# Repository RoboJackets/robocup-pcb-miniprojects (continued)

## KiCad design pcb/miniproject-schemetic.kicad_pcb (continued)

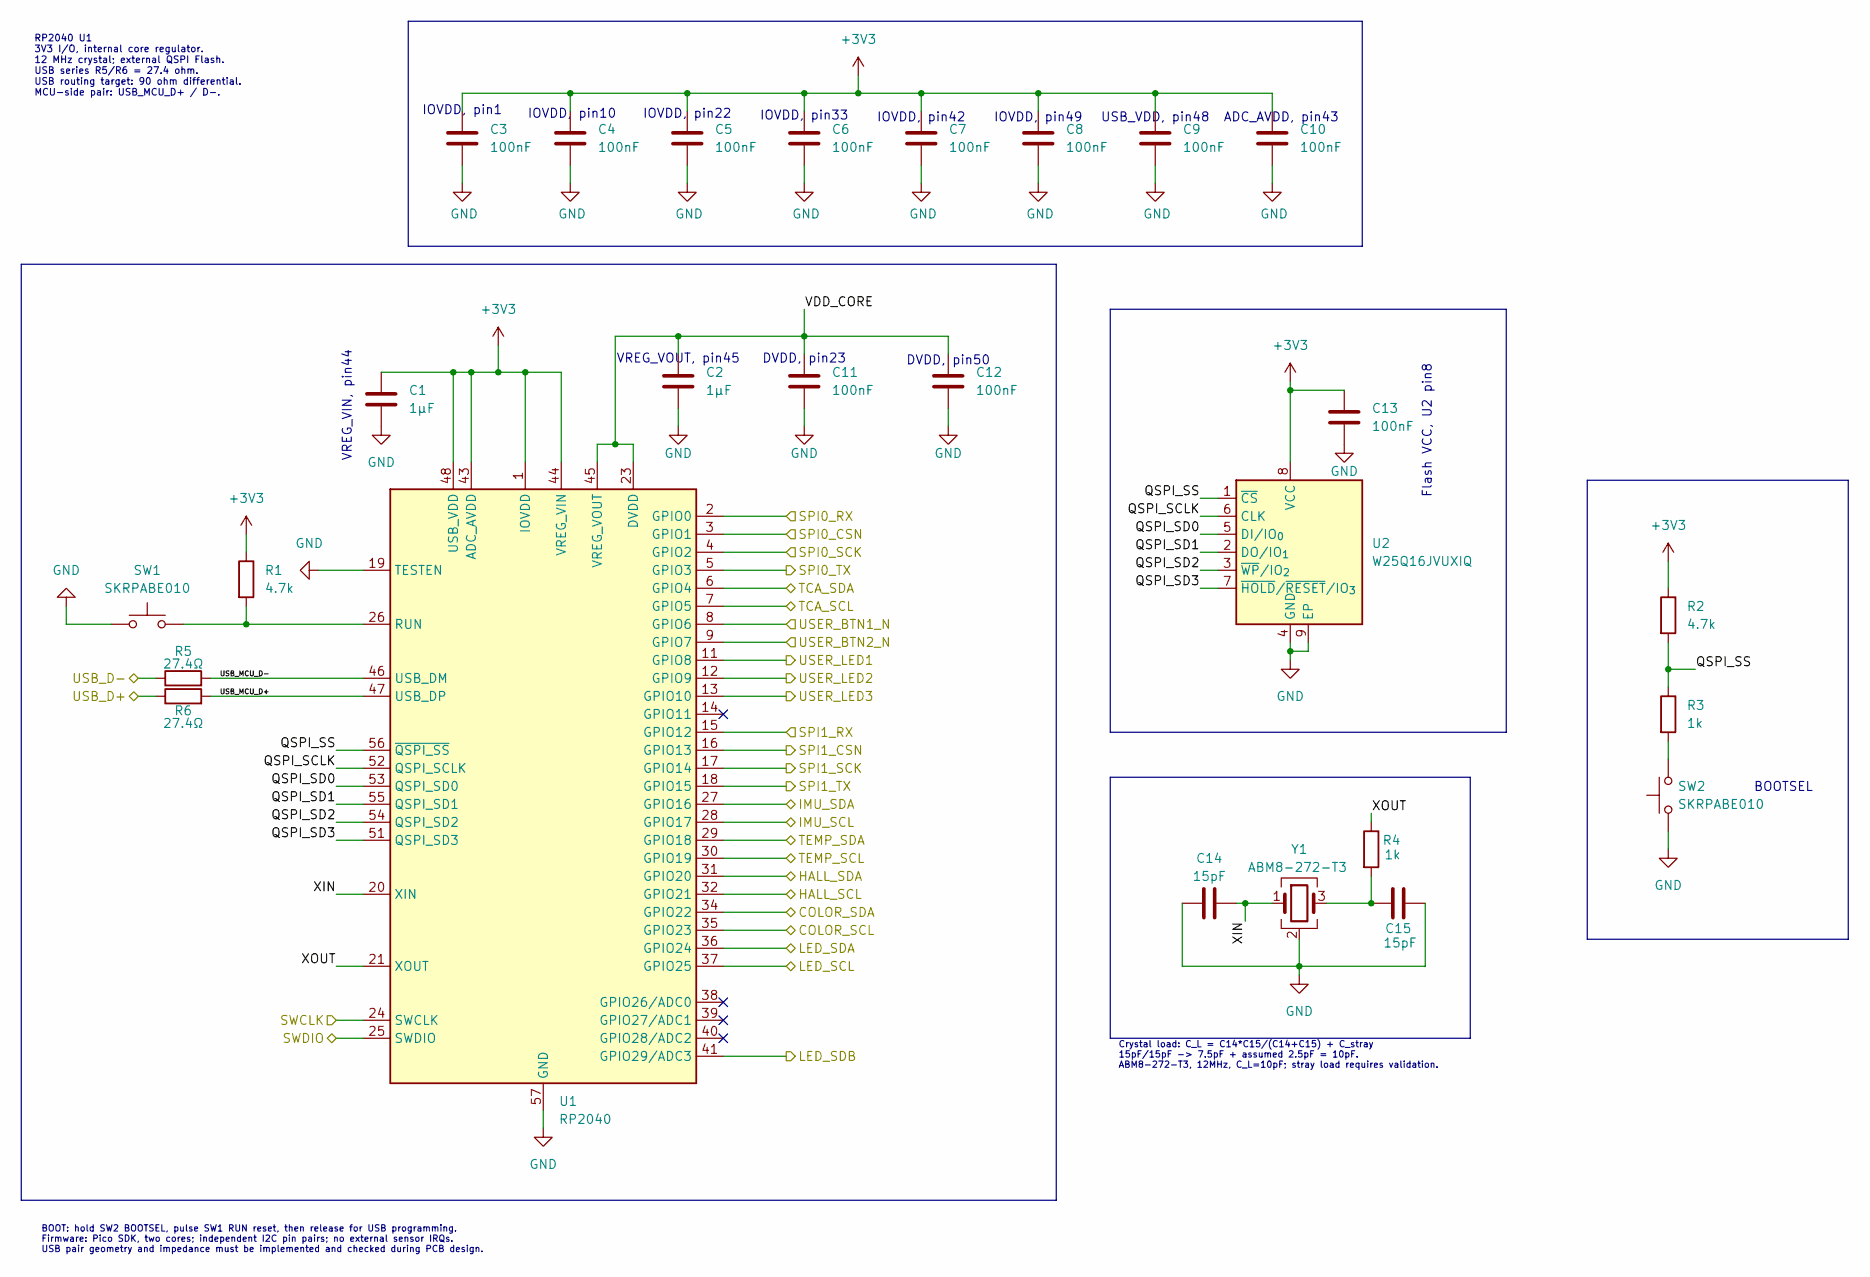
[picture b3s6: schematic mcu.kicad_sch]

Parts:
C1, C2: 1µF; C_0603_1608Metric; Tolerance 10%; Voltage 6.3V minimum
C3, C4, C5, C6, C7, C8, C9, C10, C11, C12, C13: 100nF; C_0603_1608Metric; Tolerance 10%; Voltage 6.3V minimum
C14, C15: 15pF; C_0603_1608Metric; Tolerance 5%; Voltage 6.3V minimum
R1, R2: 4.7k; R_0603_1608Metric; Tolerance 1%
R3, R4: 1k; R_0603_1608Metric; Tolerance 1%
R5, R6: 27.4Ω; R_0603_1608Metric; Tolerance 1%
SW1, SW2: SKRPABE010; SW_SPST_ALPS_SKRPABE010_4.2x3.2mm
U1: RP2040; QFN-56-1EP_7x7mm_P0.4mm_EP3.2x3.2mm
U2: W25Q16JVUXIQ; Winbond_USON-8-1EP_3x2mm_P0.5mm_EP0.2x1.6mm
Y1: ABM8-272-T3; Crystal_SMD_3225-4Pin_3.2x2.5mm

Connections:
+3V3: C1.1, C3.1, C4.1, C5.1, C6.1, C7.1, C8.1, C9.1, C10.1, C13.1, R1.1, R2.1, U1.1 (IOVDD), U1.10 (IOVDD), U1.22 (IOVDD), U1.33 (IOVDD), U1.42 (IOVDD), U1.43 (ADC_AVDD), U1.44 (VREG_VIN), U1.48 (USB_VDD), U1.49 (IOVDD), U2.8 (VCC); also elsewhere on the board
/COLOR_SCL: U1.35 (GPIO23); also elsewhere on the board
/COLOR_SDA: U1.34 (GPIO22); also elsewhere on the board
/HALL_SCL: U1.32 (GPIO21); also elsewhere on the board
/HALL_SDA: U1.31 (GPIO20); also elsewhere on the board
/IMU_SCL: U1.28 (GPIO17); also elsewhere on the board
/IMU_SDA: U1.27 (GPIO16); also elsewhere on the board
/Interfaces/USB_D+: R6.1; also elsewhere on the board
/Interfaces/USB_D-: R5.1; also elsewhere on the board
/LED_SCL: U1.37 (GPIO25); also elsewhere on the board
/LED_SDA: U1.36 (GPIO24); also elsewhere on the board
/LED_SDB: U1.41 (GPIO29/ADC3); also elsewhere on the board
/MCU/QSPI_SCLK: U1.52 (QSPI_SCLK), U2.6 (CLK)
/MCU/QSPI_SD0: U1.53 (QSPI_SD0), U2.5 (DI/IO_{0})
/MCU/QSPI_SD1: U1.55 (QSPI_SD1), U2.2 (DO/IO_{1})
/MCU/QSPI_SD2: U1.54 (QSPI_SD2), U2.3 (~WP/IO_{2})
/MCU/QSPI_SD3: U1.51 (QSPI_SD3), U2.7 (~HOLD/~RESET/IO_{3})
/MCU/QSPI_SS: R2.2, R3.1, U1.56 (~QSPI_SS), U2.1 (~CS)
/MCU/USB_MCU_D+: R6.2, U1.47 (USB_DP)
/MCU/USB_MCU_D-: R5.2, U1.46 (USB_DM)
/MCU/VDD_CORE: C2.1, C11.1, C12.1, U1.23 (DVDD), U1.45 (VREG_VOUT), U1.50 (DVDD)
/MCU/XIN: C14.2, U1.20 (XIN), Y1.1
/MCU/XOUT: R4.1, U1.21 (XOUT)
/SPI0_CSN: U1.3 (GPIO1); also elsewhere on the board
/SPI0_RX: U1.2 (GPIO0); also elsewhere on the board
/SPI0_SCK: U1.4 (GPIO2); also elsewhere on the board
/SPI0_TX: U1.5 (GPIO3); also elsewhere on the board
/SPI1_CSN: U1.16 (GPIO13); also elsewhere on the board
/SPI1_RX: U1.15 (GPIO12); also elsewhere on the board
/SPI1_SCK: U1.17 (GPIO14); also elsewhere on the board
/SPI1_TX: U1.18 (GPIO15); also elsewhere on the board
/SWCLK: U1.24 (SWCLK); also elsewhere on the board
/SWDIO: U1.25 (SWDIO); also elsewhere on the board
/TCA_SCL: U1.7 (GPIO5); also elsewhere on the board
/TCA_SDA: U1.6 (GPIO4); also elsewhere on the board
/TEMP_SCL: U1.30 (GPIO19); also elsewhere on the board
/TEMP_SDA: U1.29 (GPIO18); also elsewhere on the board
/USER_BTN1_N: U1.8 (GPIO6); also elsewhere on the board
/USER_BTN2_N: U1.9 (GPIO7); also elsewhere on the board
/USER_LED1: U1.11 (GPIO8); also elsewhere on the board
/USER_LED2: U1.12 (GPIO9); also elsewhere on the board
/USER_LED3: U1.13 (GPIO10); also elsewhere on the board
GND: C1.2, C2.2, C3.2, C4.2, C5.2, C6.2, C7.2, C8.2, C9.2, C10.2, C11.2, C12.2, C13.2, C14.1, C15.2, SW1.1, SW2.1, U1.19 (TESTEN), U1.57 (GND), U2.4 (GND), U2.9 (EP), Y1.2 (G), Y1.4 (G); also elsewhere on the board
unnamed: C15.1, R4.2, Y1.3
unnamed: R3.2, SW2.2
unnamed: R1.2, SW1.2, U1.26 (RUN)

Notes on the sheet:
DVDD, pin23
VREG_VIN, pin44
IOVDD, pin49
IOVDD, pin42
Flash VCC, U2 pin8
ADC_AVDD, pin43
DVDD, pin50
IOVDD, pin10
USB_VDD, pin48
IOVDD, pin33
IOVDD, pin22
BOOTSEL
IOVDD, pin1
VREG_VOUT, pin45
RP2040 U1 3V3 I/O, internal core regulator. 12 MHz crystal; external QSPI Flash. USB series R5/R6 = 27.4 ohm. USB routing target: 90 ohm differential. MCU-side pair: USB_MCU_D+ / D-.
Crystal load: C_L = C14*C15/(C14+C15) + C_stray 15pF/15pF -> 7.5pF + assumed 2.5pF = 10pF. ABM8-272-T3, 12MHz, C_L=10pF; stray load requires validation.
BOOT: hold SW2 BOOTSEL, pulse SW1 RUN reset, then release for USB programming. Firmware: Pico SDK, two cores; independent I2C pin pairs; no external sensor IRQs. USB pair geometry and impedance must be implemented and checked during PCB design.

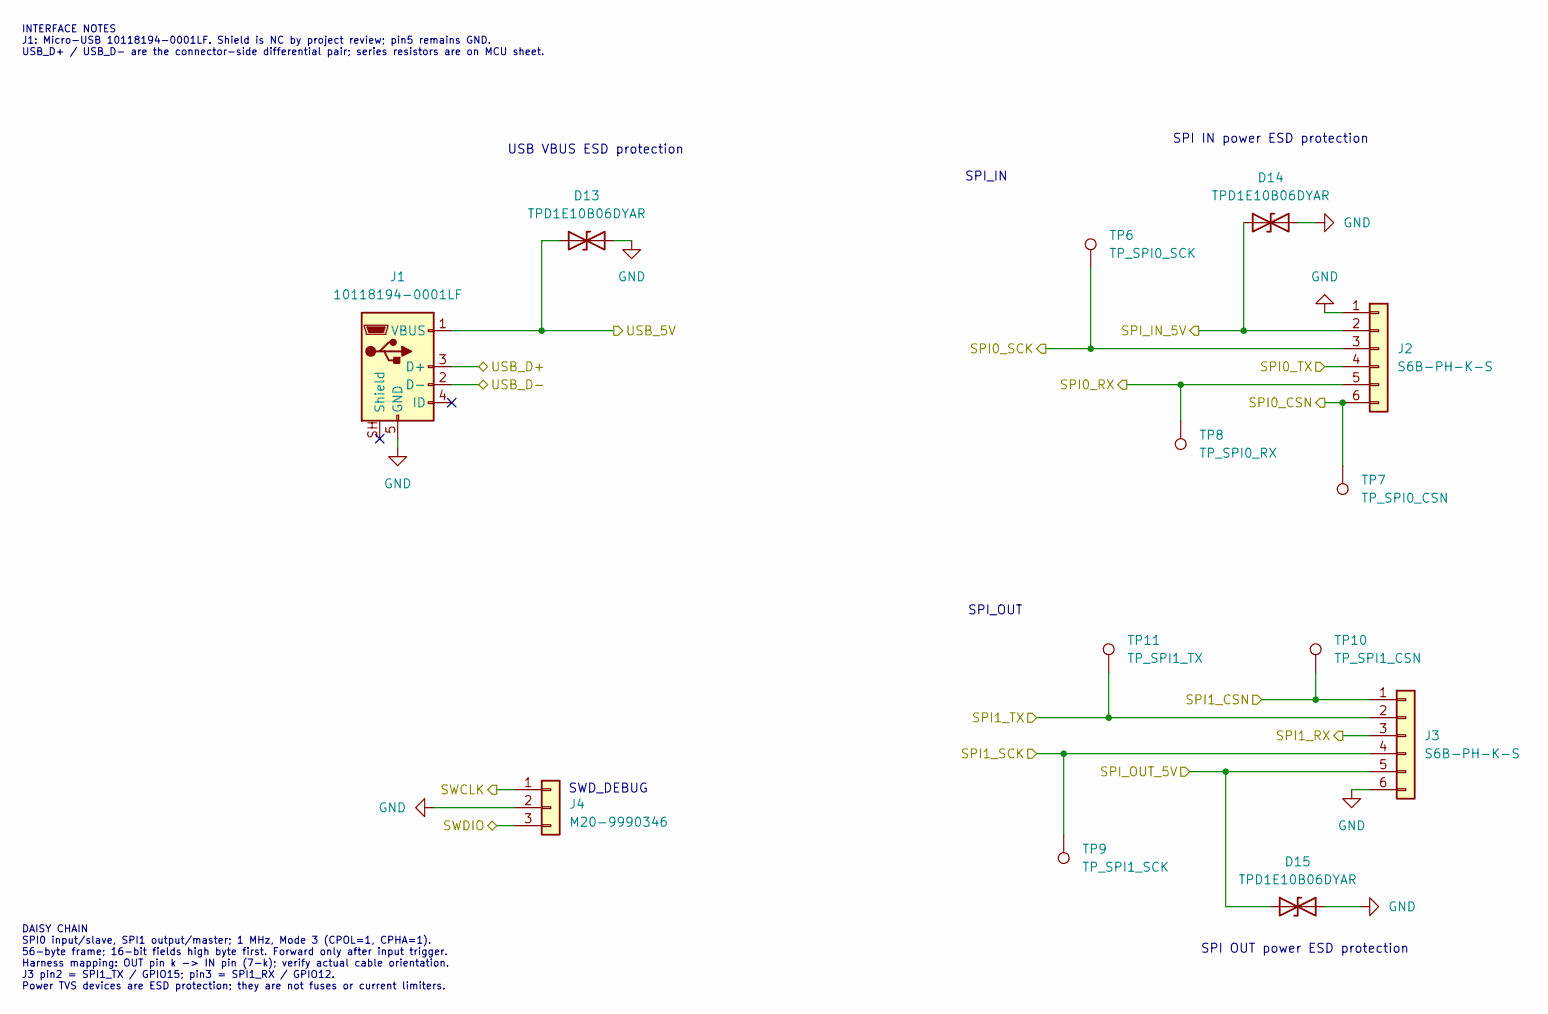
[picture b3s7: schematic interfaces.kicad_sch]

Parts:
D13, D14, D15: TPD1E10B06DYAR; D_SOD-523
J1: 10118194-0001LF; USB_Micro-B_Amphenol_10118194-0001LF_Horizontal
J2, J3: S6B-PH-K-S; JST_PH_S6B-PH-K_1x06_P2.00mm_Horizontal
J4: M20-9990346; PinHeader_1x03_P2.54mm_Vertical
TP6: TP_SPI0_SCK; TestPoint_Pad_D1.0mm
TP7: TP_SPI0_CSN; TestPoint_Pad_D1.0mm
TP8: TP_SPI0_RX; TestPoint_Pad_D1.0mm
TP9: TP_SPI1_SCK; TestPoint_Pad_D1.0mm
TP10: TP_SPI1_CSN; TestPoint_Pad_D1.0mm
TP11: TP_SPI1_TX; TestPoint_Pad_D1.0mm

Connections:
+5V: D15.1 (A1), J3.5; also elsewhere on the board
/Interfaces/USB_D+: J1.3 (D+); also elsewhere on the board
/Interfaces/USB_D-: J1.2 (D-); also elsewhere on the board
/SPI0_CSN: J2.6, TP7.1 (1_1); also elsewhere on the board
/SPI0_RX: J2.5, TP8.1 (1_1); also elsewhere on the board
/SPI0_SCK: J2.3, TP6.1 (1_1); also elsewhere on the board
/SPI0_TX: J2.4; also elsewhere on the board
/SPI1_CSN: J3.1, TP10.1 (1_1); also elsewhere on the board
/SPI1_RX: J3.3; also elsewhere on the board
/SPI1_SCK: J3.4, TP9.1 (1_1); also elsewhere on the board
/SPI1_TX: J3.2, TP11.1 (1_1); also elsewhere on the board
/SPI_IN_5V: D14.1 (A1), J2.2; also elsewhere on the board
/SWCLK: J4.1; also elsewhere on the board
/SWDIO: J4.3; also elsewhere on the board
/USB_5V: D13.1 (A1), J1.1 (VBUS); also elsewhere on the board
GND: D13.2 (A2), D14.2 (A2), D15.2 (A2), J1.5 (GND), J2.1, J3.6, J4.2; also elsewhere on the board

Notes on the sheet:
USB VBUS ESD protection
SPI_IN
SPI OUT power ESD protection
SPI IN power ESD protection
SPI_OUT
SWD_DEBUG
INTERFACE NOTES J1: Micro-USB 10118194-0001LF. Shield is NC by project review; pin5 remains GND. USB_D+ / USB_D- are the connector-side differential pair; series resistors are on MCU sheet.
DAISY CHAIN SPI0 input/slave, SPI1 output/master; 1 MHz, Mode 3 (CPOL=1, CPHA=1). 56-byte frame; 16-bit fields high byte first. Forward only after input trigger. Harness mapping: OUT pin k -> IN pin (7-k); verify actual cable orientation. J3 pin2 = SPI1_TX / GPIO15; pin3 = SPI1_RX / GPIO12. Power T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

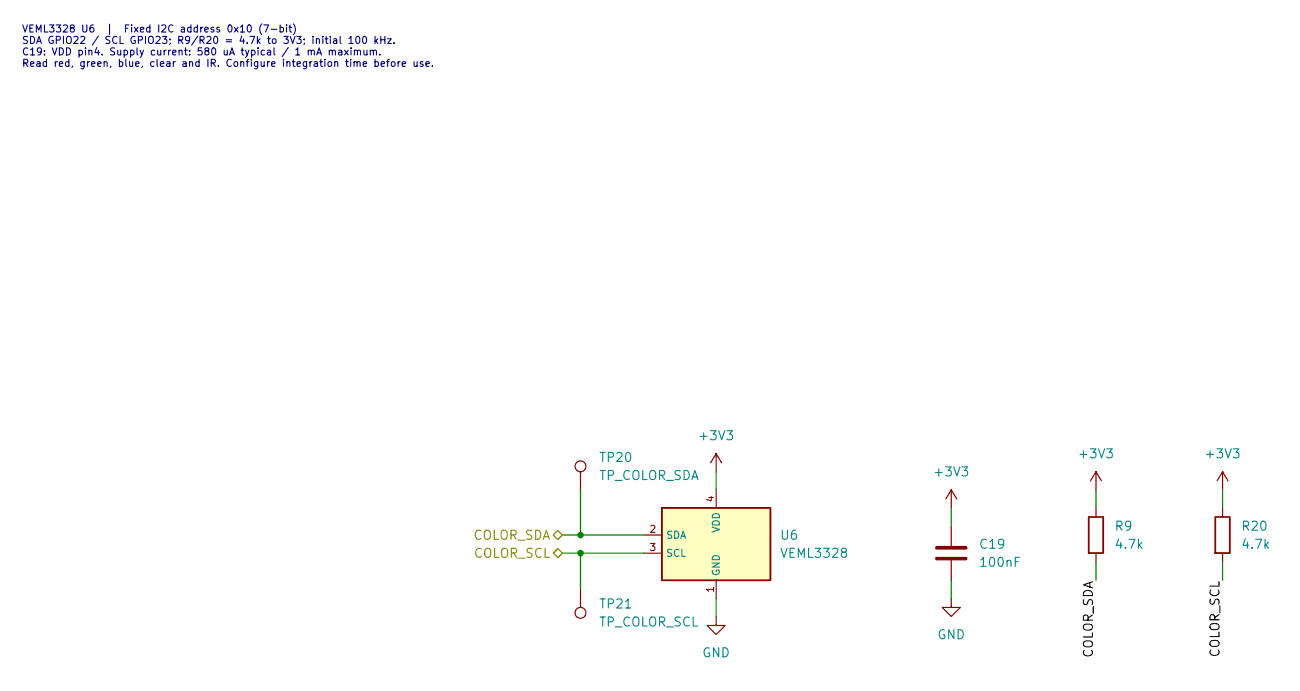
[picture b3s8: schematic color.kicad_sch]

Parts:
C19: 100nF; C_0603_1608Metric; Tolerance 10%; Voltage 6.3V minimum
R9, R20: 4.7k; R_0603_1608Metric; Tolerance 1%
TP20: TP_COLOR_SDA; TestPoint_Pad_D1.0mm
TP21: TP_COLOR_SCL; TestPoint_Pad_D1.0mm
U6: VEML3328; Vishay_VEML3328_2x1.25mm

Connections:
+3V3: C19.1, R9.1, R20.1, U6.4 (VDD); also elsewhere on the board
/COLOR_SCL: R20.2, TP21.1 (1_1), U6.3 (SCL); also elsewhere on the board
/COLOR_SDA: R9.2, TP20.1 (1_1), U6.2 (SDA); also elsewhere on the board
GND: C19.2, U6.1 (GND); also elsewhere on the board

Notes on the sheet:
VEML3328 U6 | Fixed I2C address 0x10 (7-bit) SDA GPIO22 / SCL GPIO23; R9/R20 = 4.7k to 3V3; initial 100 kHz. C19: VDD pin4. Supply current: 580 uA typical / 1 mA maximum. Read red, green, blue, clear and IR. Configure integration time before use.

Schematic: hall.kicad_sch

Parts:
C17: 100nF; C_0603_1608Metric; Tolerance 10%; Voltage 6.3V minimum
R15, R16, R17: 4.7k; R_0603_1608Metric; Tolerance 1%
TP18: TP_HALL_SCL; TestPoint_Pad_D1.0mm
TP19: TP_HALL_SDA; TestPoint_Pad_D1.0mm
U4: TMAG5273A2QDBVR; SOT-23-6

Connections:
+3V3: C17.1, R15.2, R16.1, R17.1, U4.4 (VCC); also elsewhere on the board
/HALL_SCL: R15.1, TP18.1 (1_1), U4.1 (SCL); also elsewhere on the board
/HALL_SDA: R16.2, TP19.1 (1_1), U4.6 (SDA); also elsewhere on the board
GND: C17.2, U4.2 (GND), U4.3 (TEST); also elsewhere on the board
unnamed: R17.2, U4.5 (~INT)

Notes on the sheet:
TMAG5273A2 U4 | Factory I2C address 0x35 (7-bit) SDA GPIO20 / SCL GPIO21; R15/R16 = 4.7k to 3V3; initial 100 kHz. A2 range option: +/-133 mT or +/-266 mT. Active current: 2.3 mA typical. C17: VCC pin4; TEST pin3 is GND. INT pin5 has R17 pullup only, no MCU IRQ. Firmware: INT_MODE = 0; use I2C trigg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

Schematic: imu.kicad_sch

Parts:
C20: 10nF; C_0603_1608Metric; Tolerance 10%; Voltage 6.3V minimum
C21: 100nF; C_0603_1608Metric; Tolerance 10%; Voltage 6.3V minimum
C22: 2.2µF; C_0603_1608Metric; Tolerance 10%; Voltage 6.3V minimum
R21, R22: 4.7k; R_0603_1608Metric; Tolerance 1%
TP14: TP_IMU_SDA; TestPoint_Pad_D1.0mm
TP15: TP_IMU_SCL; TestPoint_Pad_D1.0mm
U7: ICM-42605; LGA-14_3x2.5mm_P0.5mm_LayoutBorder3x4y

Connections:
+3V3: C20.1, C21.1, C22.1, R21.1, R22.1, U7.5 (VDDIO), U7.8 (VDD), U7.12 (~AP_CS); also elsewhere on the board
/IMU_SCL: R22.2, TP15.1 (1_1), U7.13 (AP_SCL); also elsewhere on the board
/IMU_SDA: R21.2, TP14.1 (1_1), U7.14 (AP_SDA); also elsewhere on the board
GND: C20.2, C21.2, C22.2, U7.1 (AP_AD0/SDO), U7.6 (GND), U7.7 (RESV), U7.9 (INT2/FSYNC); also elsewhere on the board

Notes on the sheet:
VDDIO, pin5
VDD, pin8
ICM-42605 U7 | I2C address 0x68 (7-bit), AP_AD0 pin1 = GND AP_CS pin12 = 3V3 for I2C. SDA GPIO16 / SCL GPIO17; R21/R22 = 4.7k. Initial bus speed 100 kHz. AP_AD0 is an input in this configuration. INT1 pin4 is NC. Pin9 is unused FSYNC: GND per TDK pin-function table. Firmware must keep pin9 as an in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

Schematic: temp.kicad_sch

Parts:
C18: 100nF; C_0603_1608Metric; Tolerance 10%; Voltage 6.3V minimum
R18, R19: 4.7k; R_0603_1608Metric; Tolerance 1%
TP16: TP_TEMP_SDA; TestPoint_Pad_D1.0mm
TP17: TP_TEMP_SCL; TestPoint_Pad_D1.0mm
U5: LM75ADP; TSSOP-8_3x3mm_P0.65mm

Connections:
+3V3: C18.1, R18.1, R19.1, U5.8 (VCC); also elsewhere on the board
/TEMP_SCL: R19.2, TP17.1 (1_1), U5.2 (SCL); also elsewhere on the board
/TEMP_SDA: R18.2, TP16.1 (1_1), U5.1 (SDA); also elsewhere on the board
GND: C18.2, U5.4 (GND), U5.5 (A2), U5.6 (A1), U5.7 (A0); also elsewhere on the board

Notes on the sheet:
LM75ADP U5 | I2C address 0x48 (7-bit), A2:A0 = 000 SDA GPIO18 / SCL GPIO19; R18/R19 = 4.7k to 3V3; initial 100 kHz. C18: VCC pin8. OS pin3 is NC; poll temperature over I2C. Supply current: 100 uA typical with inactive bus; 1 mA maximum with active bus. NXP LM75A register format: signed temperature;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

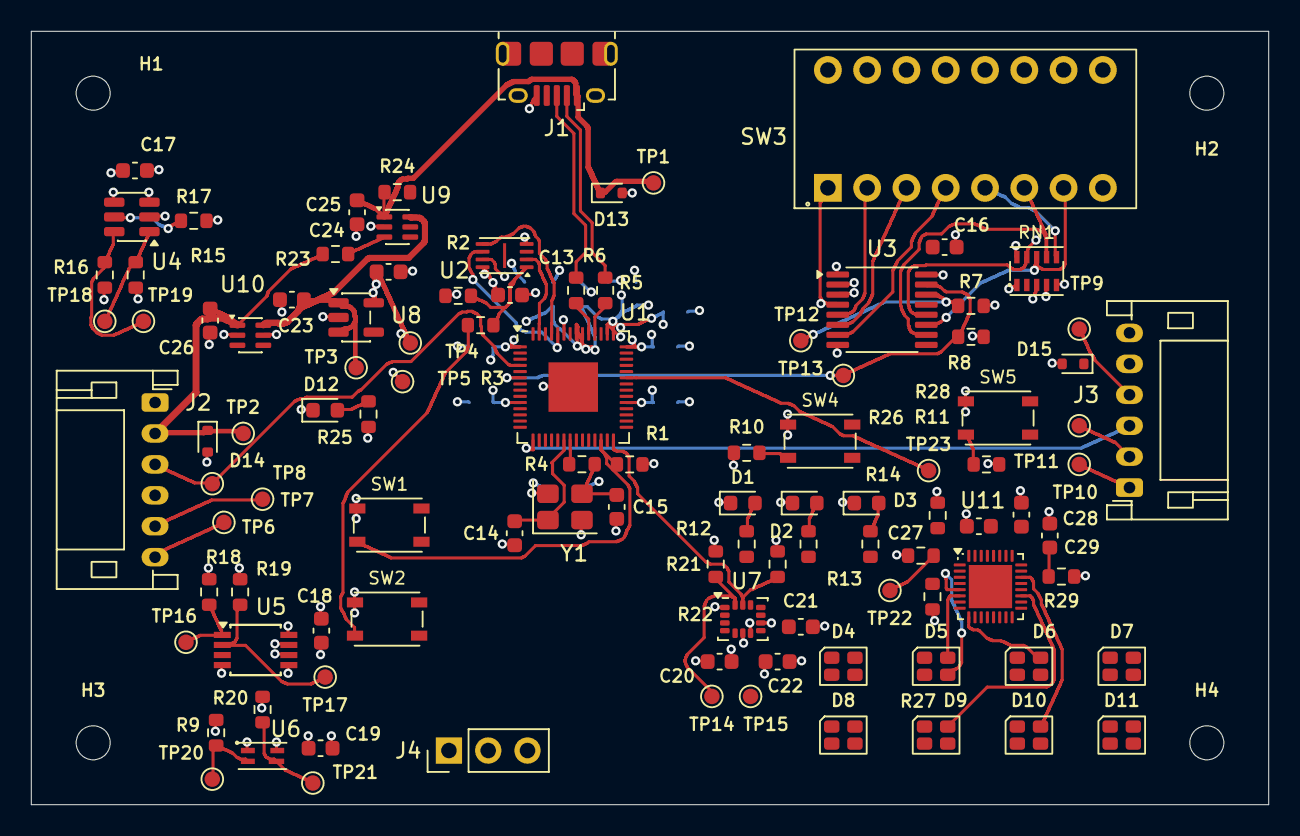
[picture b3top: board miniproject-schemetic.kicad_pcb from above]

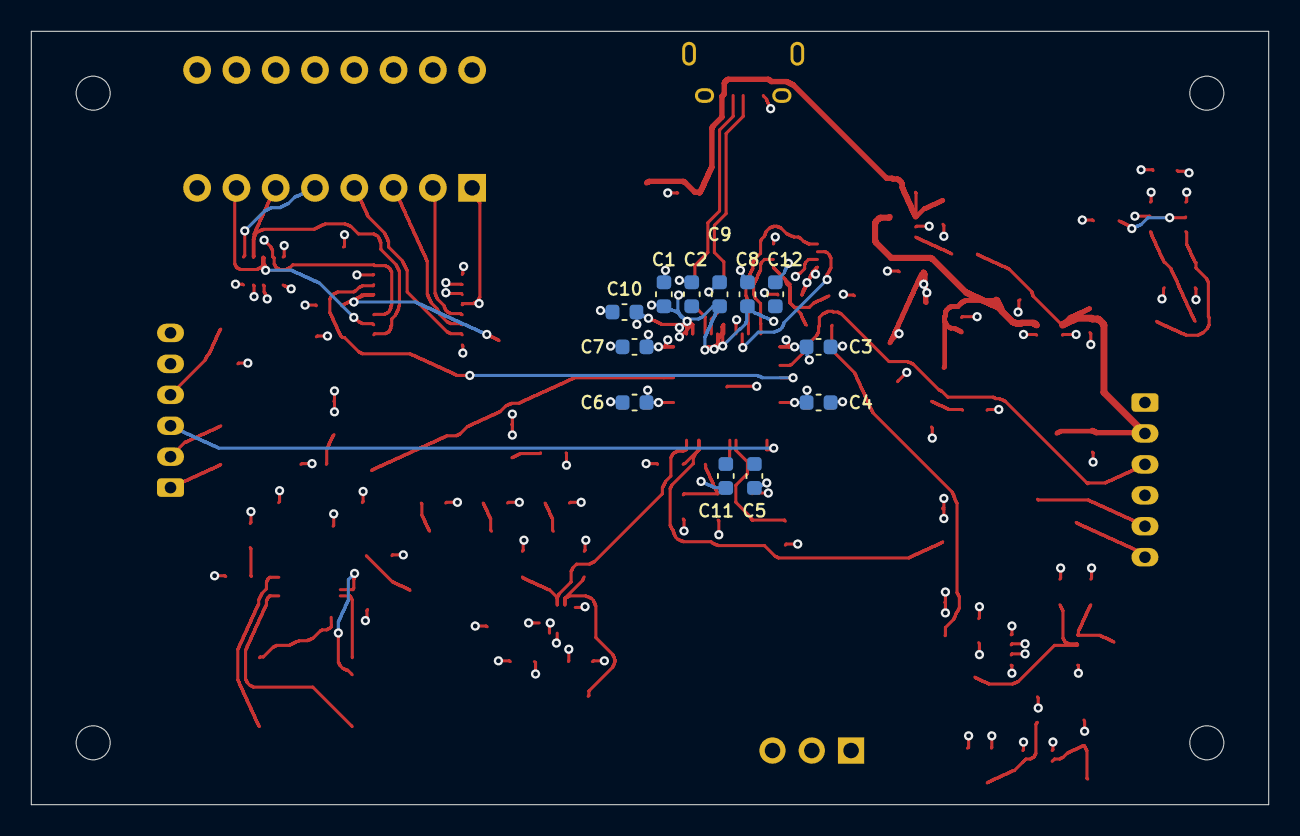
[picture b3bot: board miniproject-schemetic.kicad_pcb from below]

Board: 4 copper layers, 80.0 x 50.0 mm, 122 parts (12 on the bottom side), 89 nets.

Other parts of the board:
H1, H2, H3, H4: MountingHole_2.2mm_M2

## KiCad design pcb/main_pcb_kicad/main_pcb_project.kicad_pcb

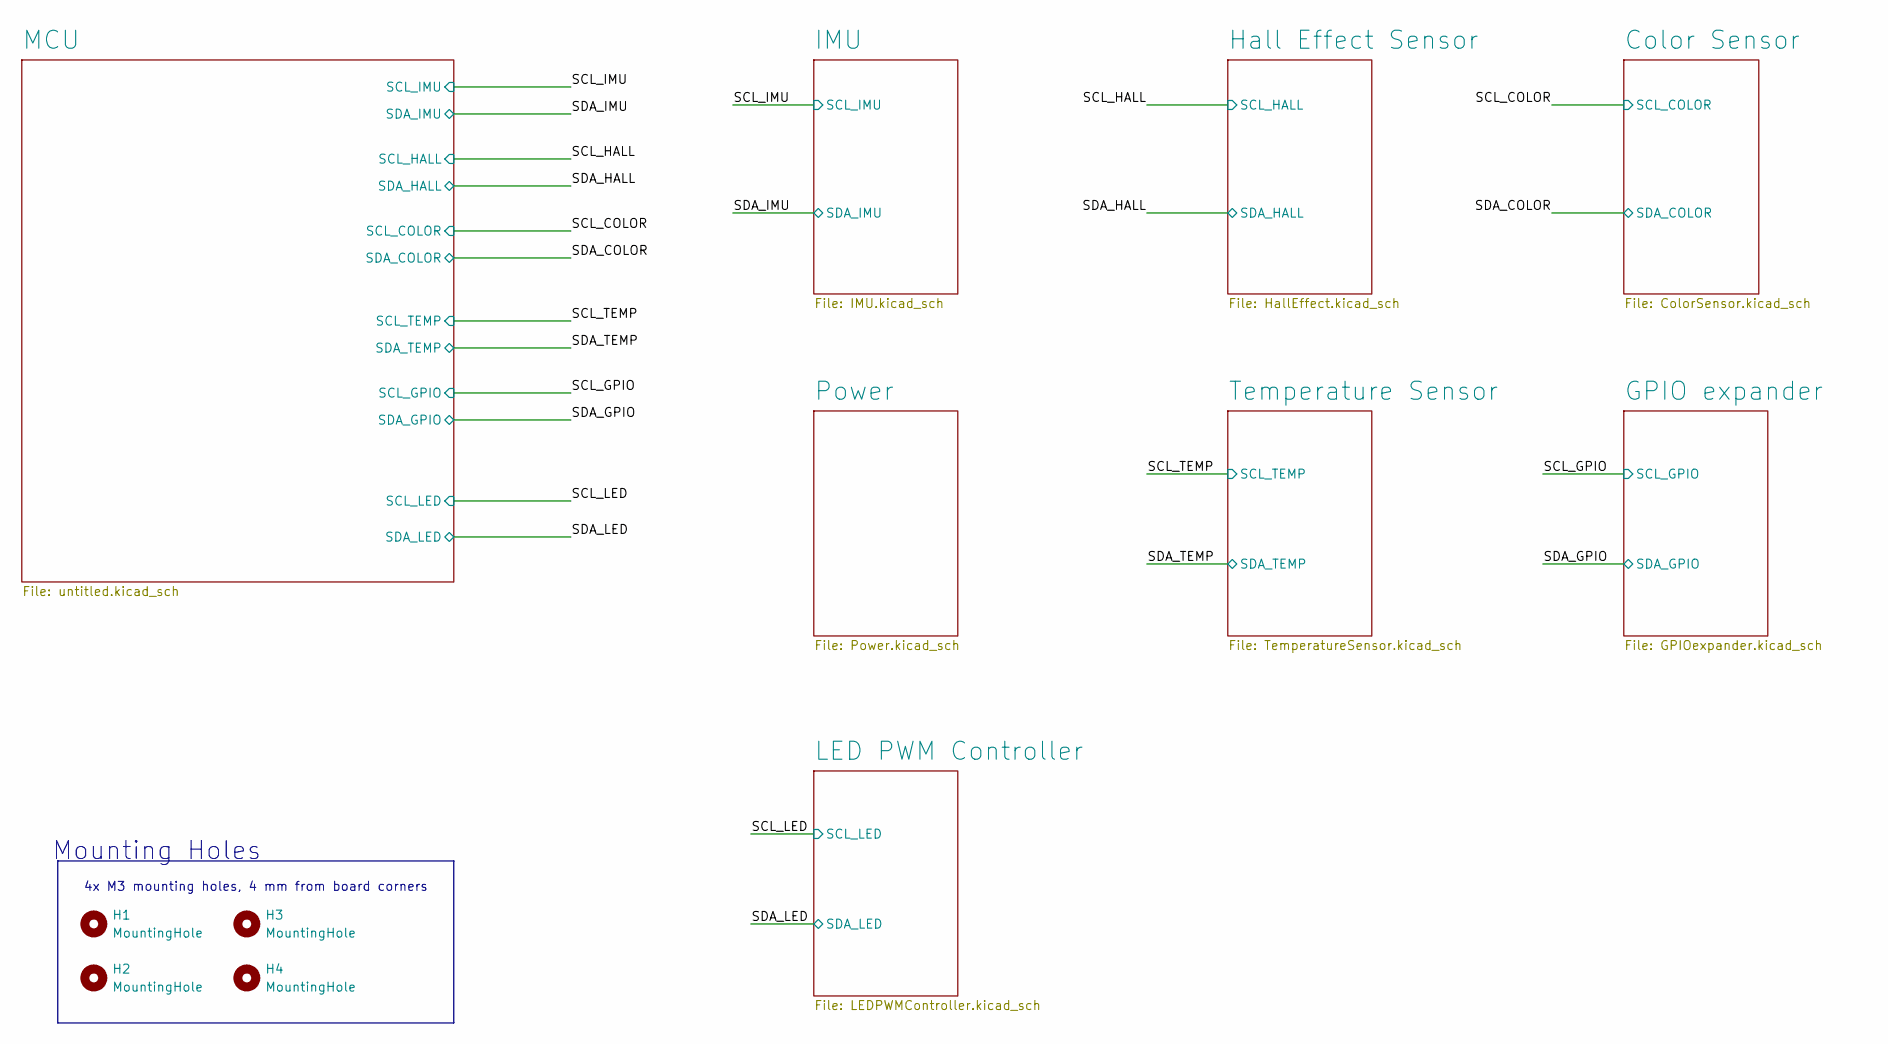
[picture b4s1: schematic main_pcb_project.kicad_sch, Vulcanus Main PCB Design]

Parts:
H1, H2, H3, H4: MountingHole; MountingHole_3.2mm_M3

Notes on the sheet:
Mounting Holes
4x M3 mounting holes, 4 mm from board corners

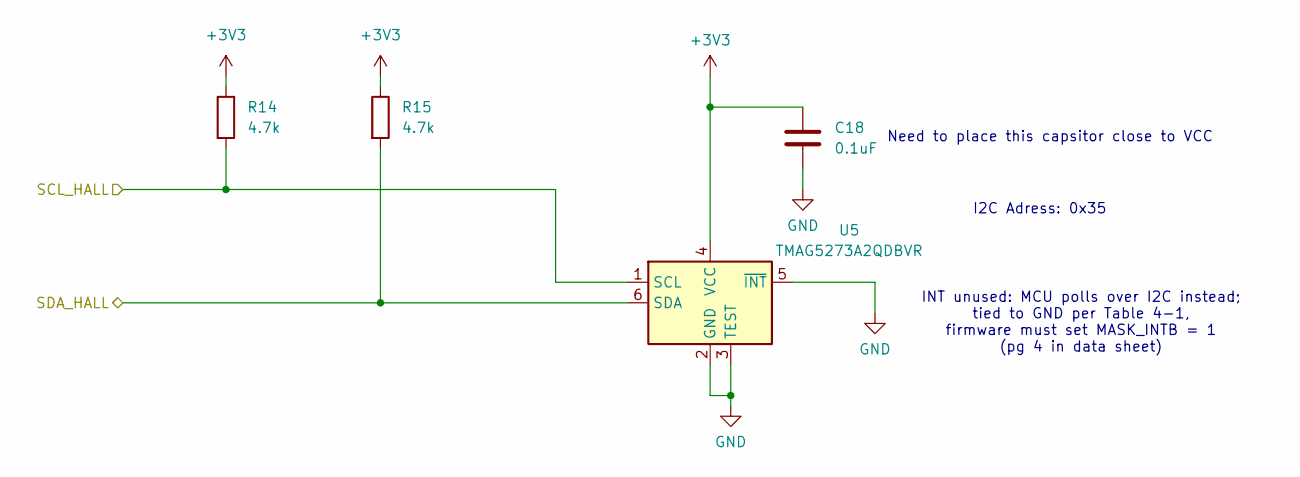
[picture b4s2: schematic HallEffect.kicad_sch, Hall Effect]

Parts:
C18: 0.1uF; C_0603_1608Metric; Manufacturer P/N CL10B104KB8NNNC
R14, R15: 4.7k; R_0402_1005Metric; Manufacturer P/N RC0402FR-074K7L
U5: TMAG5273A2QDBVR; SOT-23-6; Manufacturer P/N TMAG5273A2QDBVR

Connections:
+3V3: C18.1, R14.1, R15.1, U5.4 (VCC); also elsewhere on the board
/SCL_HALL: R14.2, U5.1 (SCL); also elsewhere on the board
/SDA_HALL: R15.2, U5.6 (SDA); also elsewhere on the board
GND: C18.2, U5.2 (GND), U5.3 (TEST), U5.5 (~INT); also elsewhere on the board

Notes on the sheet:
INT unused: MCU polls over I2C instead; tied to GND per Table 4-1, firmware must set MASK_INTB = 1 (pg 4 in data sheet)
Need to place this capsitor close to VCC
I2C Adress: 0x35

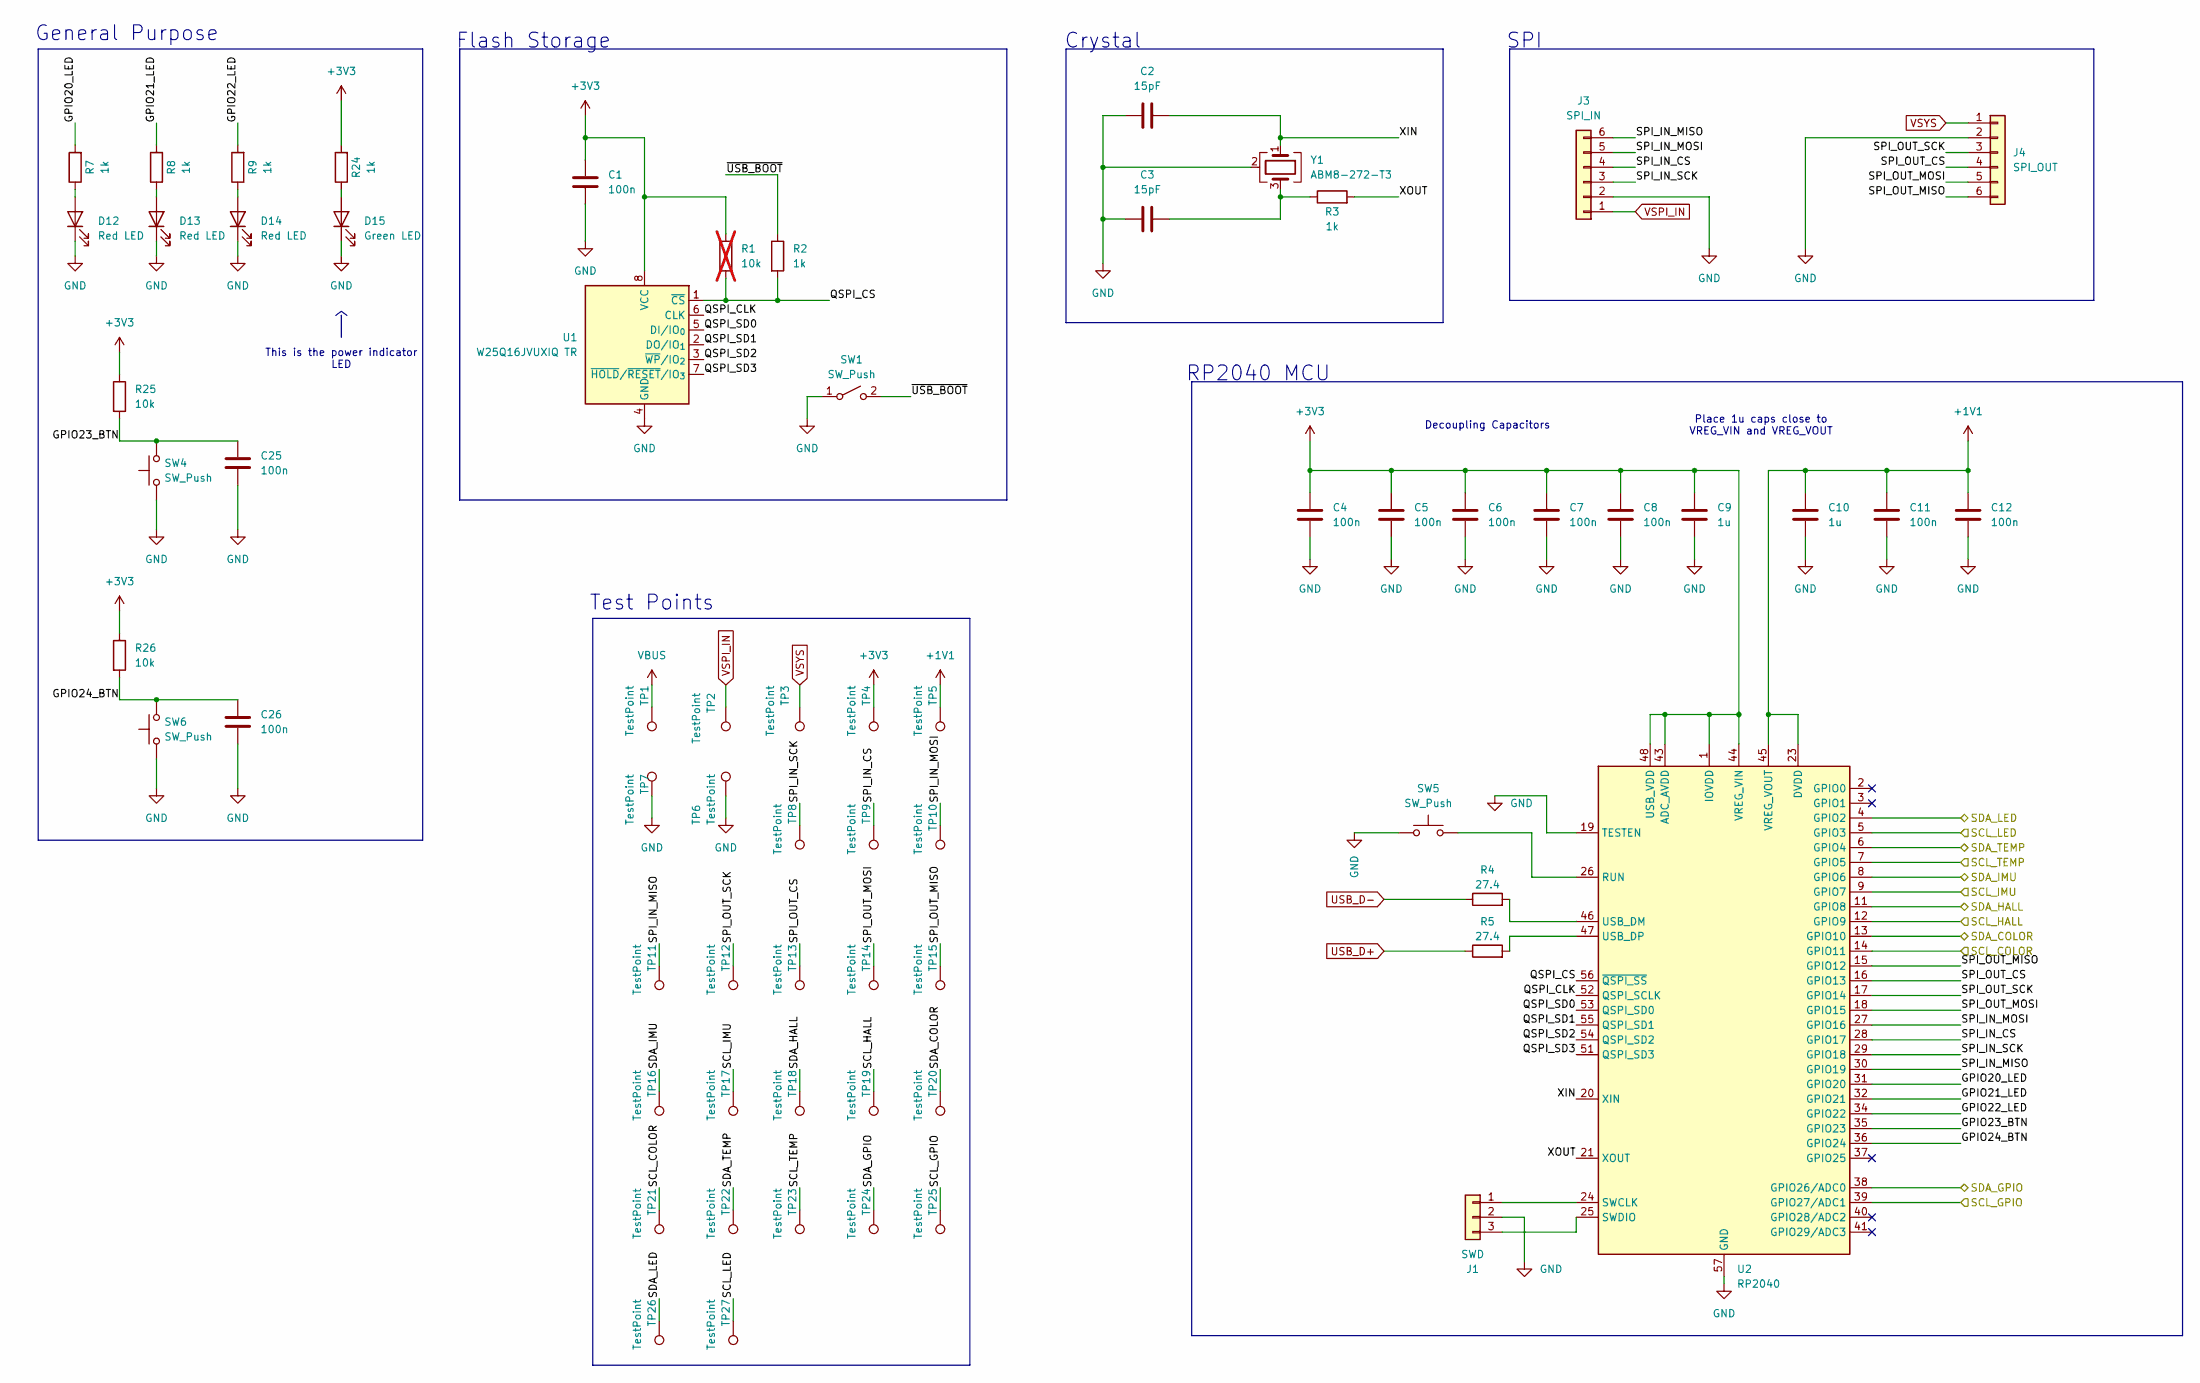
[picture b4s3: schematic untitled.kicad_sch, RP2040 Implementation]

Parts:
C1: 100n; C_0402_1005Metric
C2, C3: 15pF; C_0603_1608Metric; Manufacturer P/N C0603C150F5GACTU
C4, C5, C6, C7, C8, C11, C12: 100n; C_0402_1005Metric; Manufacturer P/N CC0603KRX7R9BB104
C9, C10: 1u; C_0402_1005Metric; Manufacturer P/N CL10A105KO8NNNC
C25, C26: 100n; C_0603_1608Metric; Manufacturer P/N CC0603KRX7R9BB104
D12, D13, D14: Red LED; LED_0603_1608Metric; Manufacturer P/N LTST-C191KRKT
D15: Green LED; LED_0603_1608Metric; Manufacturer P/N LTST-C191KGKT
J1: SWD; PinHeader_1x03_P2.54mm_Vertical; Manufacturer P/N PRPC003SAAN-RC
J3: SPI_IN; JST_PH_S6B-PH-K_1x06_P2.00mm_Horizontal; Manufacturer P/N S6B-PH-K-S
J4: SPI_OUT; JST_PH_S6B-PH-K_1x06_P2.00mm_Horizontal; Manufacturer P/N S6B-PH-K-S
R1: 10k; R_0402_1005Metric; Manufacturer P/N RC0402FR-0710KL; not fitted
R2, R3, R7, R8, R9, R24: 1k; R_0402_1005Metric; Manufacturer P/N RC0402FR-071KL
R4, R5: 27.4; R_0402_1005Metric; Manufacturer P/N RC0402FR-0727R4L
R25, R26: 10k; R_0402_1005Metric; Manufacturer P/N RC0402FR-0710KL
SW1: SW_Push; SW_SKRPACE010_AAL; Manufacturer P/N SKRPACE010
SW4, SW5, SW6: SW_Push; SW_SKRPACE010_AAL; Manufacturer P/N SKRPABE010
TP1, TP2, TP3, TP4, TP5, TP6, TP7, TP8, TP9, TP10, TP11, TP12, TP13, TP14, TP15, TP16, TP17, TP18, TP19, TP20, TP21, TP22, TP23, TP24, TP25, TP26, TP27: TestPoint; TestPoint_Pad_D1.0mm
U1: W25Q16JVUXIQ TR; Winbond_USON-8-1EP_3x2mm_P0.5mm_EP0.2x1.6mm; Manufacturer P/N W25Q16JVUXIQ TR
U2: RP2040; QFN-56-1EP_7x7mm_P0.4mm_EP3.2x3.2mm; Manufacturer P/N SC0914(13)
Y1: ABM8-272-T3; Crystal_SMD_3225-4Pin_3.2x2.5mm; Manufacturer P/N ABM8-272-T3

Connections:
+1V1: C10.1, C11.1, C12.1, TP5.1 (1_1), U2.23 (DVDD), U2.45 (VREG_VOUT), U2.50 (DVDD)
+3V3: C1.1, C4.1, C5.1, C6.1, C7.1, C8.1, C9.1, R1.1, R24.2, R25.1, R26.1, TP4.1 (1_1), U1.8 (VCC), U2.1 (IOVDD), U2.10 (IOVDD), U2.22 (IOVDD), U2.33 (IOVDD), U2.42 (IOVDD), U2.43 (ADC_AVDD), U2.44 (VREG_VIN), U2.48 (USB_VDD), U2.49 (IOVDD); also elsewhere on the board
/MCU/GPIO20_LED: R7.2, U2.31 (GPIO20)
/MCU/GPIO21_LED: R8.2, U2.32 (GPIO21)
/MCU/GPIO22_LED: R9.2, U2.34 (GPIO22)
/MCU/GPIO23_BTN: C25.1, R25.2, SW4.2, U2.35 (GPIO23)
/MCU/GPIO24_BTN: C26.1, R26.2, SW6.2, U2.36 (GPIO24)
/MCU/QSPI_CLK: U1.6 (CLK), U2.52 (QSPI_SCLK)
/MCU/QSPI_CS: R1.2, R2.2, U1.1 (~CS), U2.56 (~QSPI_SS)
/MCU/QSPI_SD0: U1.5 (DI/IO_{0}), U2.53 (QSPI_SD0)
/MCU/QSPI_SD1: U1.2 (DO/IO_{1}), U2.55 (QSPI_SD1)
/MCU/QSPI_SD2: U1.3 (~WP/IO_{2}), U2.54 (QSPI_SD2)
/MCU/QSPI_SD3: U1.7 (~HOLD/~RESET/IO_{3}), U2.51 (QSPI_SD3)
/MCU/SPI_IN_CS: J3.4, TP9.1 (1_1), U2.28 (GPIO17)
/MCU/SPI_IN_MISO: J3.6, TP11.1 (1_1), U2.30 (GPIO19)
/MCU/SPI_IN_MOSI: J3.5, TP10.1 (1_1), U2.27 (GPIO16)
/MCU/SPI_IN_SCK: J3.3, TP8.1 (1_1), U2.29 (GPIO18)
/MCU/SPI_OUT_CS: J4.4, TP13.1 (1_1), U2.16 (GPIO13)
/MCU/SPI_OUT_MISO: J4.6, TP15.1 (1_1), U2.15 (GPIO12)
/MCU/SPI_OUT_MOSI: J4.5, TP14.1 (1_1), U2.18 (GPIO15)
/MCU/SPI_OUT_SCK: J4.3, TP12.1 (1_1), U2.17 (GPIO14)
/MCU/XIN: C2.2, U2.20 (XIN), Y1.1
/MCU/XOUT: R3.2, U2.21 (XOUT)
/MCU/~USB_BOOT: R2.1, SW1.2 (B)
/SCL_COLOR: TP21.1 (1_1), U2.14 (GPIO11); also elsewhere on the board
/SCL_GPIO: TP25.1 (1_1), U2.39 (GPIO27/ADC1); also elsewhere on the board
/SCL_HALL: TP19.1 (1_1), U2.12 (GPIO9); also elsewhere on the board
/SCL_IMU: TP17.1 (1_1), U2.9 (GPIO7); also elsewhere on the board
/SCL_LED: TP27.1 (1_1), U2.5 (GPIO3); also elsewhere on the board
/SCL_TEMP: TP23.1 (1_1), U2.7 (GPIO5); also elsewhere on the board
/SDA_COLOR: TP20.1 (1_1), U2.13 (GPIO10); also elsewhere on the board
/SDA_GPIO: TP24.1 (1_1), U2.38 (GPIO26/ADC0); also elsewhere on the board
/SDA_HALL: TP18.1 (1_1), U2.11 (GPIO8); also elsewhere on the board
/SDA_IMU: TP16.1 (1_1), U2.8 (GPIO6); also elsewhere on the board
/SDA_LED: TP26.1 (1_1), U2.4 (GPIO2); also elsewhere on the board
/SDA_TEMP: TP22.1 (1_1), U2.6 (GPIO4); also elsewhere on the board
GND: C1.2, C2.1, C3.1, C4.2, C5.2, C6.2, C7.2, C8.2, C9.2, C10.2, C11.2, C12.2, C25.2, C26.2, D12.1 (K), D13.1 (K), D14.1 (K), D15.1 (K), J1.2, J3.2, J4.2, SW1.1 (A), SW4.1, SW5.1, SW6.1, TP6.1 (1_1), TP7.1 (1_1), U1.4 (GND), U2.19 (TESTEN), U2.57 (GND), Y1.2 (G), Y1.4 (G); also elsewhere on the board
unnamed: C3.2, R3.1, Y1.3
unnamed: D12.2 (A), R7.1
unnamed: D13.2 (A), R8.1
unnamed: D14.2 (A), R9.1
unnamed: D15.2 (A), R24.1
unnamed: J1.1, U2.24 (SWCLK)
unnamed: J1.3, U2.25 (SWDIO)
unnamed: SW5.2, U2.26 (RUN)
unnamed: R4.2, U2.46 (USB_DM)
unnamed: R5.2, U2.47 (USB_DP)
USB_D+: R5.1; also elsewhere on the board
USB_D-: R4.1; also elsewhere on the board
VBUS: TP1.1 (1_1); also elsewhere on the board
VSPI_IN: J3.1, TP2.1 (1_1); also elsewhere on the board
VSYS: J4.1, TP3.1 (1_1); also elsewhere on the board

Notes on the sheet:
General Purpose
Crystal
SPI
RP2040 MCU
Test Points
Place 1u caps close to VREG_VIN and VREG_VOUT
Decoupling Capacitors
This is the power indicator LED
Flash Storage

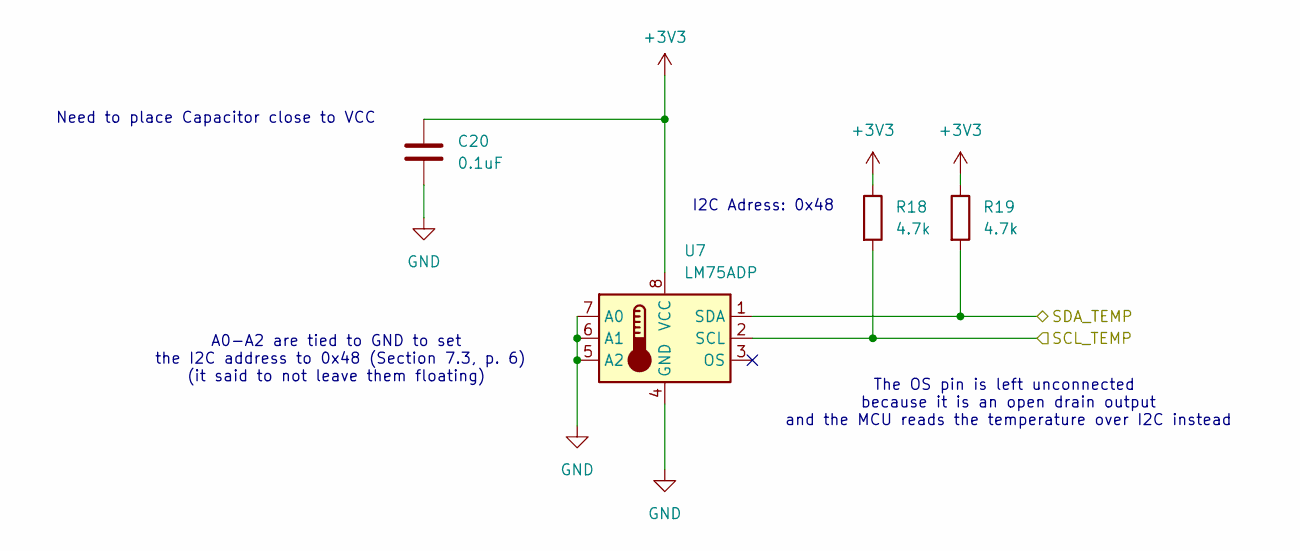
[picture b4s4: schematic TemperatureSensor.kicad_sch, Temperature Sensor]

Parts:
C20: 0.1uF; C_0603_1608Metric; Manufacturer P/N CL10B104KB8NNNC
R18, R19: 4.7k; R_0402_1005Metric; Manufacturer P/N RC0402FR-074K7L
U7: LM75ADP; TSSOP-8_3x3mm_P0.65mm; Manufacturer P/N LM75ADP,118

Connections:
+3V3: C20.1, R18.1, R19.1, U7.8 (VCC); also elsewhere on the board
/SCL_TEMP: R18.2, U7.2 (SCL); also elsewhere on the board
/SDA_TEMP: R19.2, U7.1 (SDA); also elsewhere on the board
GND: C20.2, U7.4 (GND), U7.5 (A2), U7.6 (A1), U7.7 (A0); also elsewhere on the board

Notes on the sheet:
I2C Adress: 0x48
The OS pin is left unconnected because it is an open drain output and the MCU reads the temperature over I2C instead
A0-A2 are tied to GND to set the I2C address to 0x48 (Section 7.3, p. 6) (it said to not leave them floating)
Need to place Capacitor close to VCC
